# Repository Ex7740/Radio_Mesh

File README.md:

# Radio Mesh

A custom mesh network utilising 2.4GHz radio nodes using microcontrollers and nrf24l01

There are 3 types of node:

# Basic node: 
Simply just the microcontroller and nrf24l01 modules 

# Sensor node: 
More complex, Houses the microcontroller and nrf24l01, plus a varity of sensors, dependant on the application

# Storage node: 
Houses a Flash chip to hold sensor data and other data

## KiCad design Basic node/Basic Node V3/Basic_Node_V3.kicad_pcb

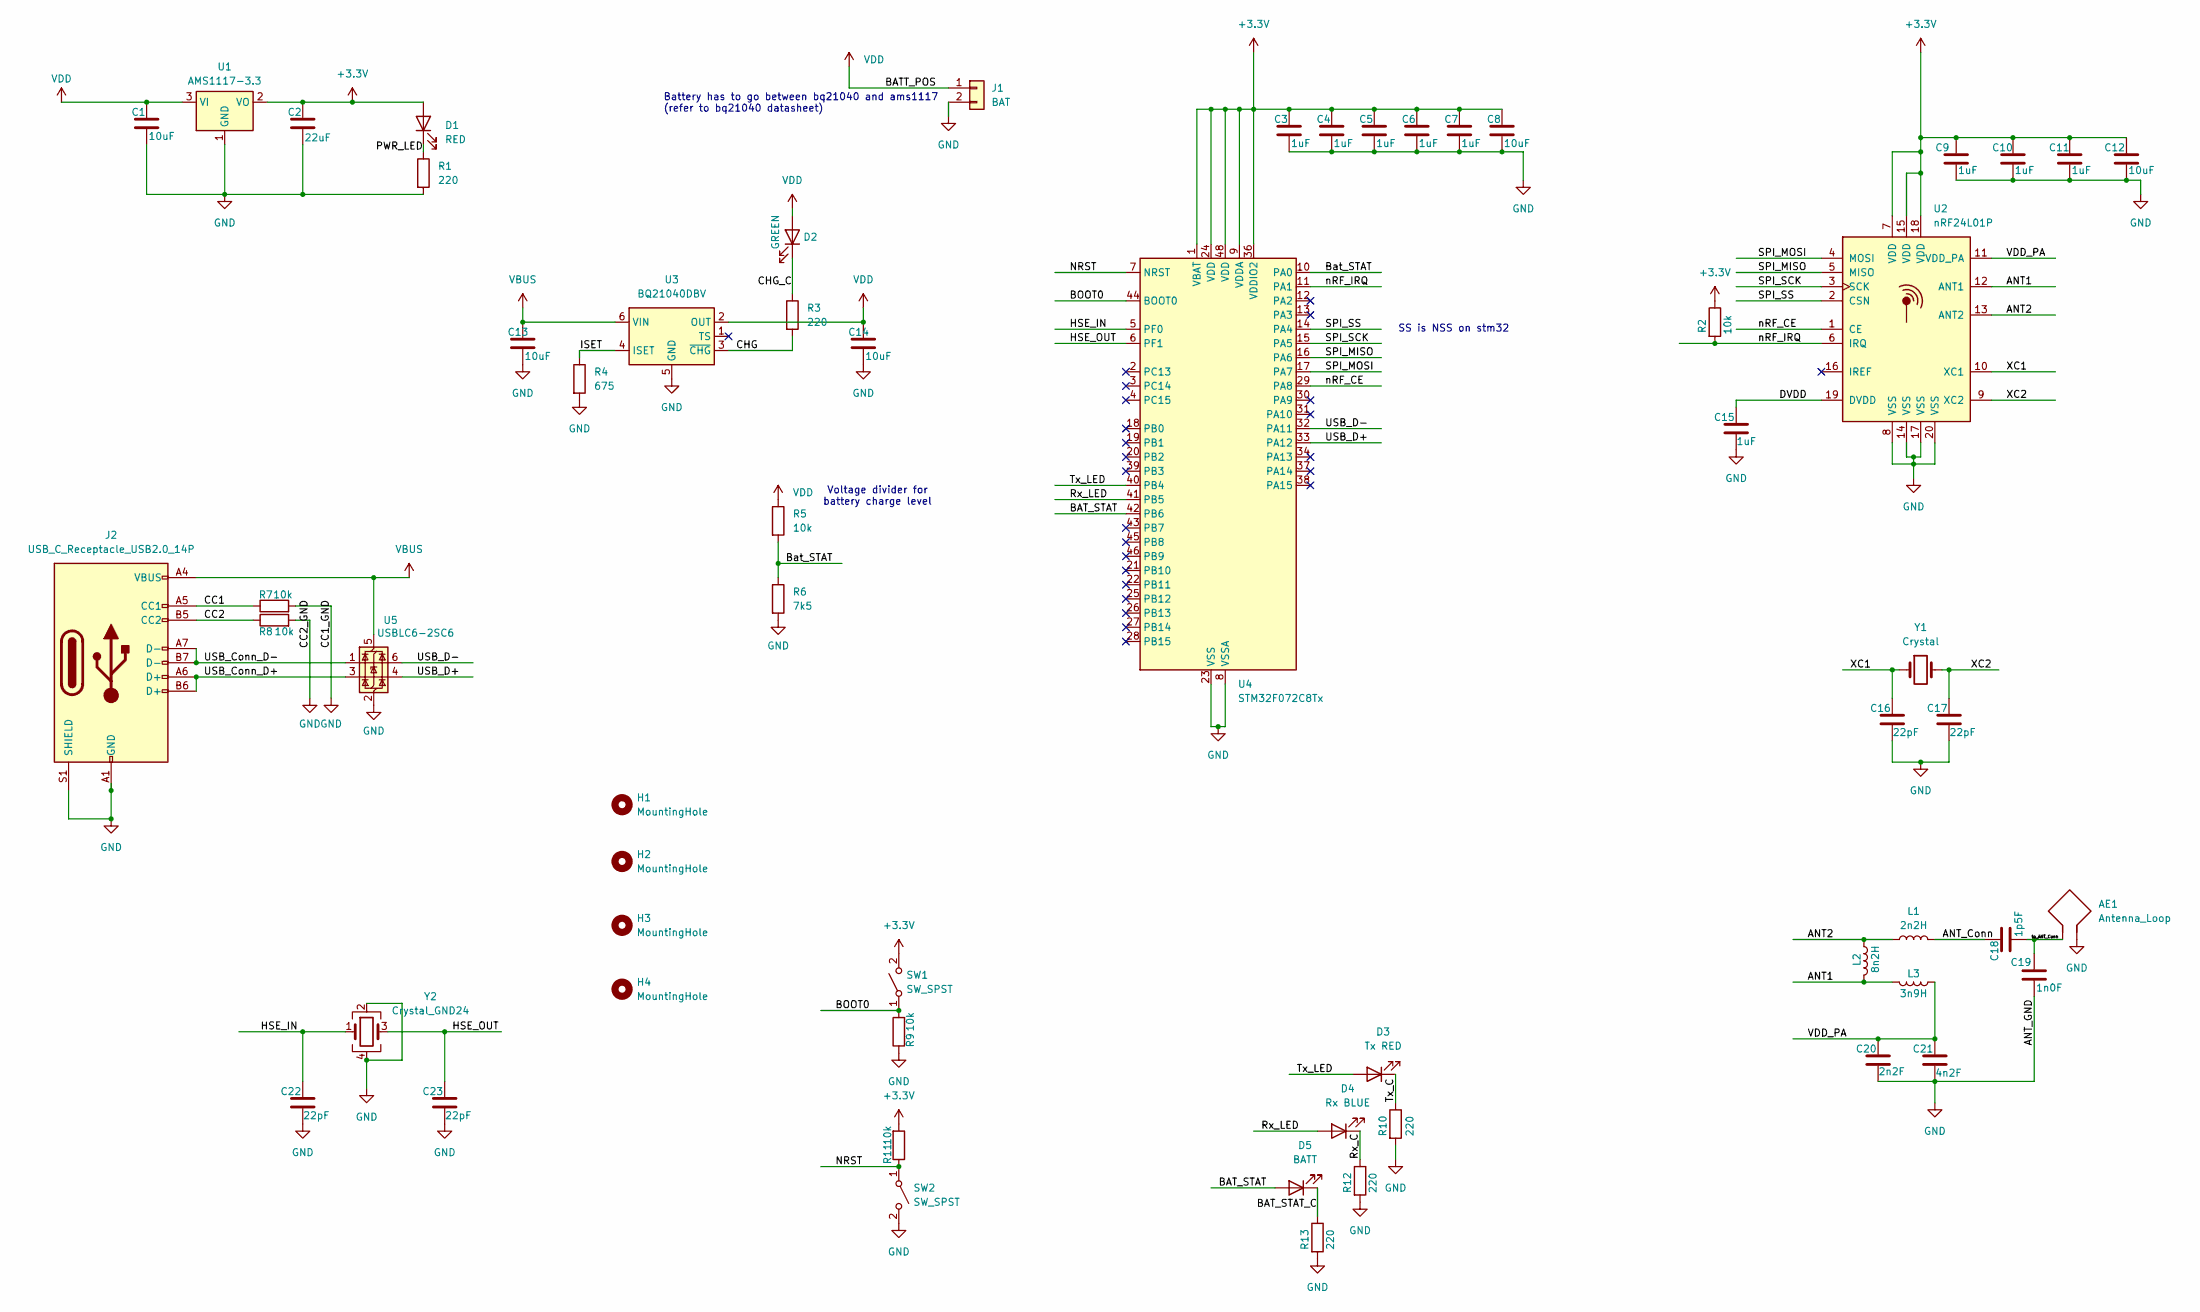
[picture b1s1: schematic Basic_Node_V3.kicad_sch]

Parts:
AE1: Antenna_Loop; Texas_SWRA117D_2.4GHz_Left
C1, C14: 10uF; C_0402_1005Metric
C2: 22uF; C_0402_1005Metric
C3, C4, C5, C6, C7, C9, C10, C11, C15: 1uF; C_0402_1005Metric
C8, C12, C13: 10uF; C_0603_1608Metric
C16, C17, C22, C23: 22pF; C_0402_1005Metric
C18: 1p5F; C_0402_1005Metric
C19: 1n0F; C_0402_1005Metric
C20: 2n2F; C_0402_1005Metric
C21: 4n2F; C_0402_1005Metric
D1: RED; LED_0603_1608Metric
D2: GREEN; LED_0603_1608Metric
D3: Tx RED; LED_0805_2012Metric
D4: Rx BLUE; LED_0805_2012Metric
D5: BATT; LED_0805_2012Metric
H1, H2, H3, H4: MountingHole; MountingHole_2.2mm_M2
J1: BAT; JST_PH_S2B-PH-K_1x02_P2.00mm_Horizontal
J2: USB_C_Receptacle_USB2.0_14P; USB_C_Receptacle_HRO_TYPE-C-31-M-12
L1: 2n2H; L_0603_1608Metric
L2: 8n2H; L_0603_1608Metric
L3: 3n9H; L_0603_1608Metric
R1, R3, R10, R12, R13: 220; R_0603_1608Metric
R2, R5, R8, R9, R11: 10k; R_0603_1608Metric
R4: 675; R_0603_1608Metric
R6: 7k5; R_0603_1608Metric
R7: 10k; L_0603_1608Metric
SW1, SW2: SW_SPST; SW_PUSH_6mm
U1: AMS1117-3.3; SOT-223-3_TabPin2
U2: nRF24L01P; QFN-20-1EP_4x4mm_P0.5mm_EP2.5x2.5mm
U3: BQ21040DBV; SOT-23-6
U4: STM32F072C8Tx; LQFP-48_7x7mm_P0.5mm
U5: USBLC6-2SC6; SOT-23-6
Y1: Crystal; Crystal_SMD_0603-2Pin_6.0x3.5mm
Y2: Crystal_GND24; Crystal_SMD_0603-4Pin_6.0x3.5mm

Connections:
+3.3V: C2.1, C3.1, C4.1, C5.1, C6.1, C7.1, C8.1, C9.1, C10.1, C11.1, C12.1, D1.2 (A), R2.1, R11.2, SW1.2 (B), U1.2 (VO), U2.7 (VDD), U2.15 (VDD), U2.18 (VDD), U4.1 (VBAT), U4.9 (VDDA), U4.24 (VDD), U4.36 (VDDIO2), U4.48 (VDD)
/ANT1: L2.2, L3.2, U2.12 (ANT1)
/ANT2: L1.1, L2.1, U2.13 (ANT2)
/ANT_Conn: C18.1, L1.2
/BAT_STAT: D5.2 (A), U4.42 (PB6)
/BAT_STAT_C: D5.1 (K), R13.1
/BOOT0: R9.2, SW1.1 (A), U4.44 (BOOT0)
/Bat_STAT: R5.2, R6.1, U4.10 (PA0)
/CC1: J2.A5 (CC1), R7.1
/CC2: J2.B5 (CC2), R8.1
/CHG: R3.2, U3.3 (~CHG)
/CHG_C: D2.1 (K), R3.1
/DVDD: C15.1, U2.19 (DVDD)
/HSE_IN: C22.1, U4.5 (PF0), Y2.1
/HSE_OUT: C23.1, U4.6 (PF1), Y2.3
/ISET: R4.1, U3.4 (ISET)
/NRST: R11.1, SW2.1 (A), U4.7 (NRST)
/PWR_LED: D1.1 (K), R1.1
/Rx_C: D4.1 (K), R12.1
/Rx_LED: D4.2 (A), U4.41 (PB5)
/SPI_MISO: U2.5 (MISO), U4.16 (PA6)
/SPI_MOSI: U2.4 (MOSI), U4.17 (PA7)
/SPI_SCK: U2.3 (SCK), U4.15 (PA5)
/SPI_SS: U2.2 (CSN), U4.14 (PA4)
/Tx_C: D3.1 (K), R10.1
/Tx_LED: D3.2 (A), U4.40 (PB4)
/USB_Conn_D+: J2.A6 (D+), J2.B6 (D+), U5.3 (I/O2)
/USB_Conn_D-: J2.A7 (D-), J2.B7 (D-), U5.1 (I/O1)
/USB_D+: U4.33 (PA12), U5.4 (I/O2)
/USB_D-: U4.32 (PA11), U5.6 (I/O1)
/VDD_PA: C20.1, C21.1, L3.1, U2.11 (VDD_PA)
/XC1: C16.1, U2.10 (XC1), Y1.1
/XC2: C17.1, U2.9 (XC2), Y1.2
/nRF_CE: U2.1 (CE), U4.29 (PA8)
/nRF_IRQ: R2.2, U2.6 (IRQ), U4.11 (PA1)
/to_ANT_Conn: AE1.1, C18.2, C19.1
GND: AE1.2, C1.2, C2.2, C3.2, C4.2, C5.2, C6.2, C7.2, C8.2, C9.2, C10.2, C11.2, C12.2, C13.2, C14.2, C15.2, C16.2, C17.2, C19.2, C20.2, C21.2, C22.2, C23.2, J1.2, J2.A1 (GND), J2.A12 (GND), J2.B1 (GND), J2.B12 (GND), J2.S1 (SHIELD), R1.2, R4.2, R6.2, R7.2, R8.2, R9.1, R10.2, R12.2, R13.2, SW2.2 (B), U1.1 (GND), U2.8 (VSS), U2.14 (VSS), U2.17 (VSS), U2.20 (VSS), U3.5 (GND), U4.8 (VSSA), U4.23 (VSS), U4.35 (VSS), U4.47 (VSS), U5.2 (GND), Y2.2, Y2.4
VBUS: C13.1, J2.A4 (VBUS), J2.A9 (VBUS), J2.B4 (VBUS), J2.B9 (VBUS), U3.6 (VIN), U5.5 (VBUS)
VDD: C1.1, C14.1, D2.2 (A), J1.1, R5.1, U1.3 (VI), U3.2 (OUT)

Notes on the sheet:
Voltage divider for battery charge level
Battery has to go between bq21040 and ams1117 (refer to bq21040 datasheet)
SS is NSS on stm32

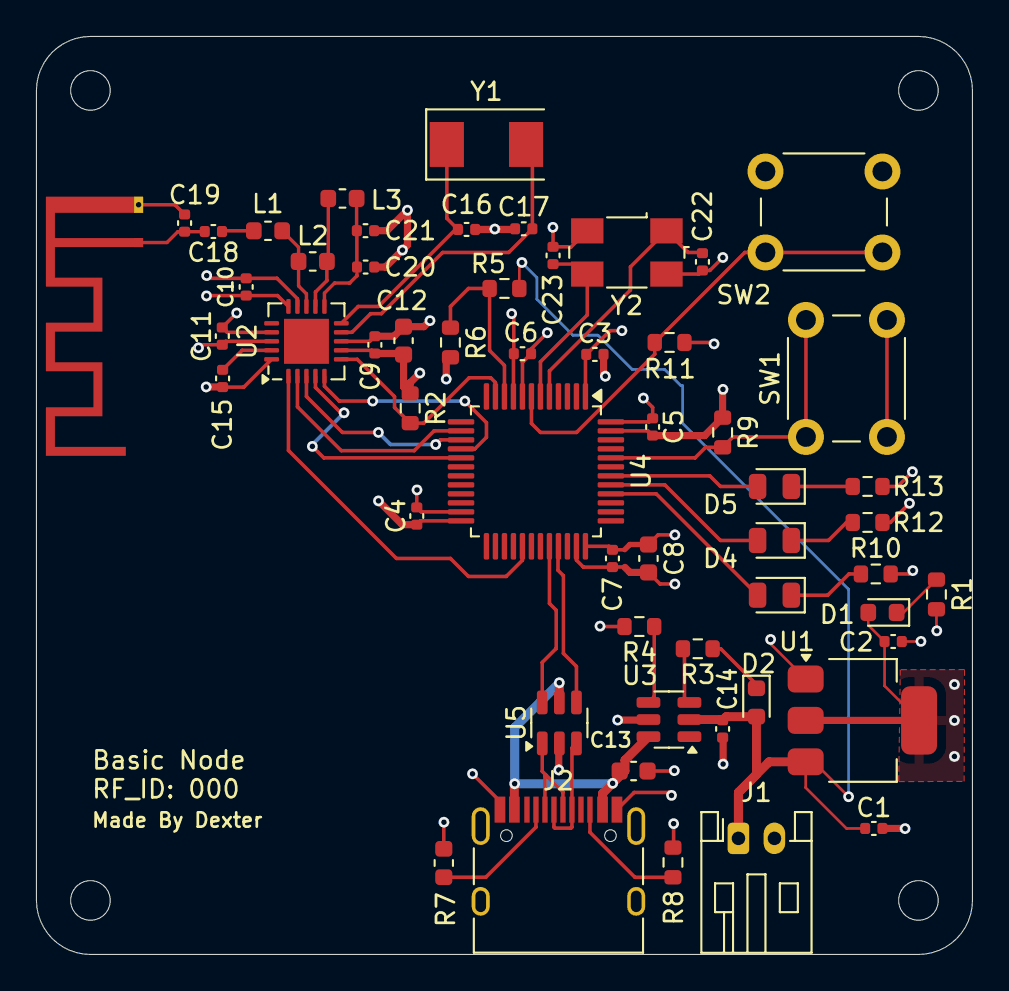
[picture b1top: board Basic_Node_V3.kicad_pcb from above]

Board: 4 copper layers, 52.0 x 51.0 mm, 60 parts (0 on the bottom side), 39 nets.

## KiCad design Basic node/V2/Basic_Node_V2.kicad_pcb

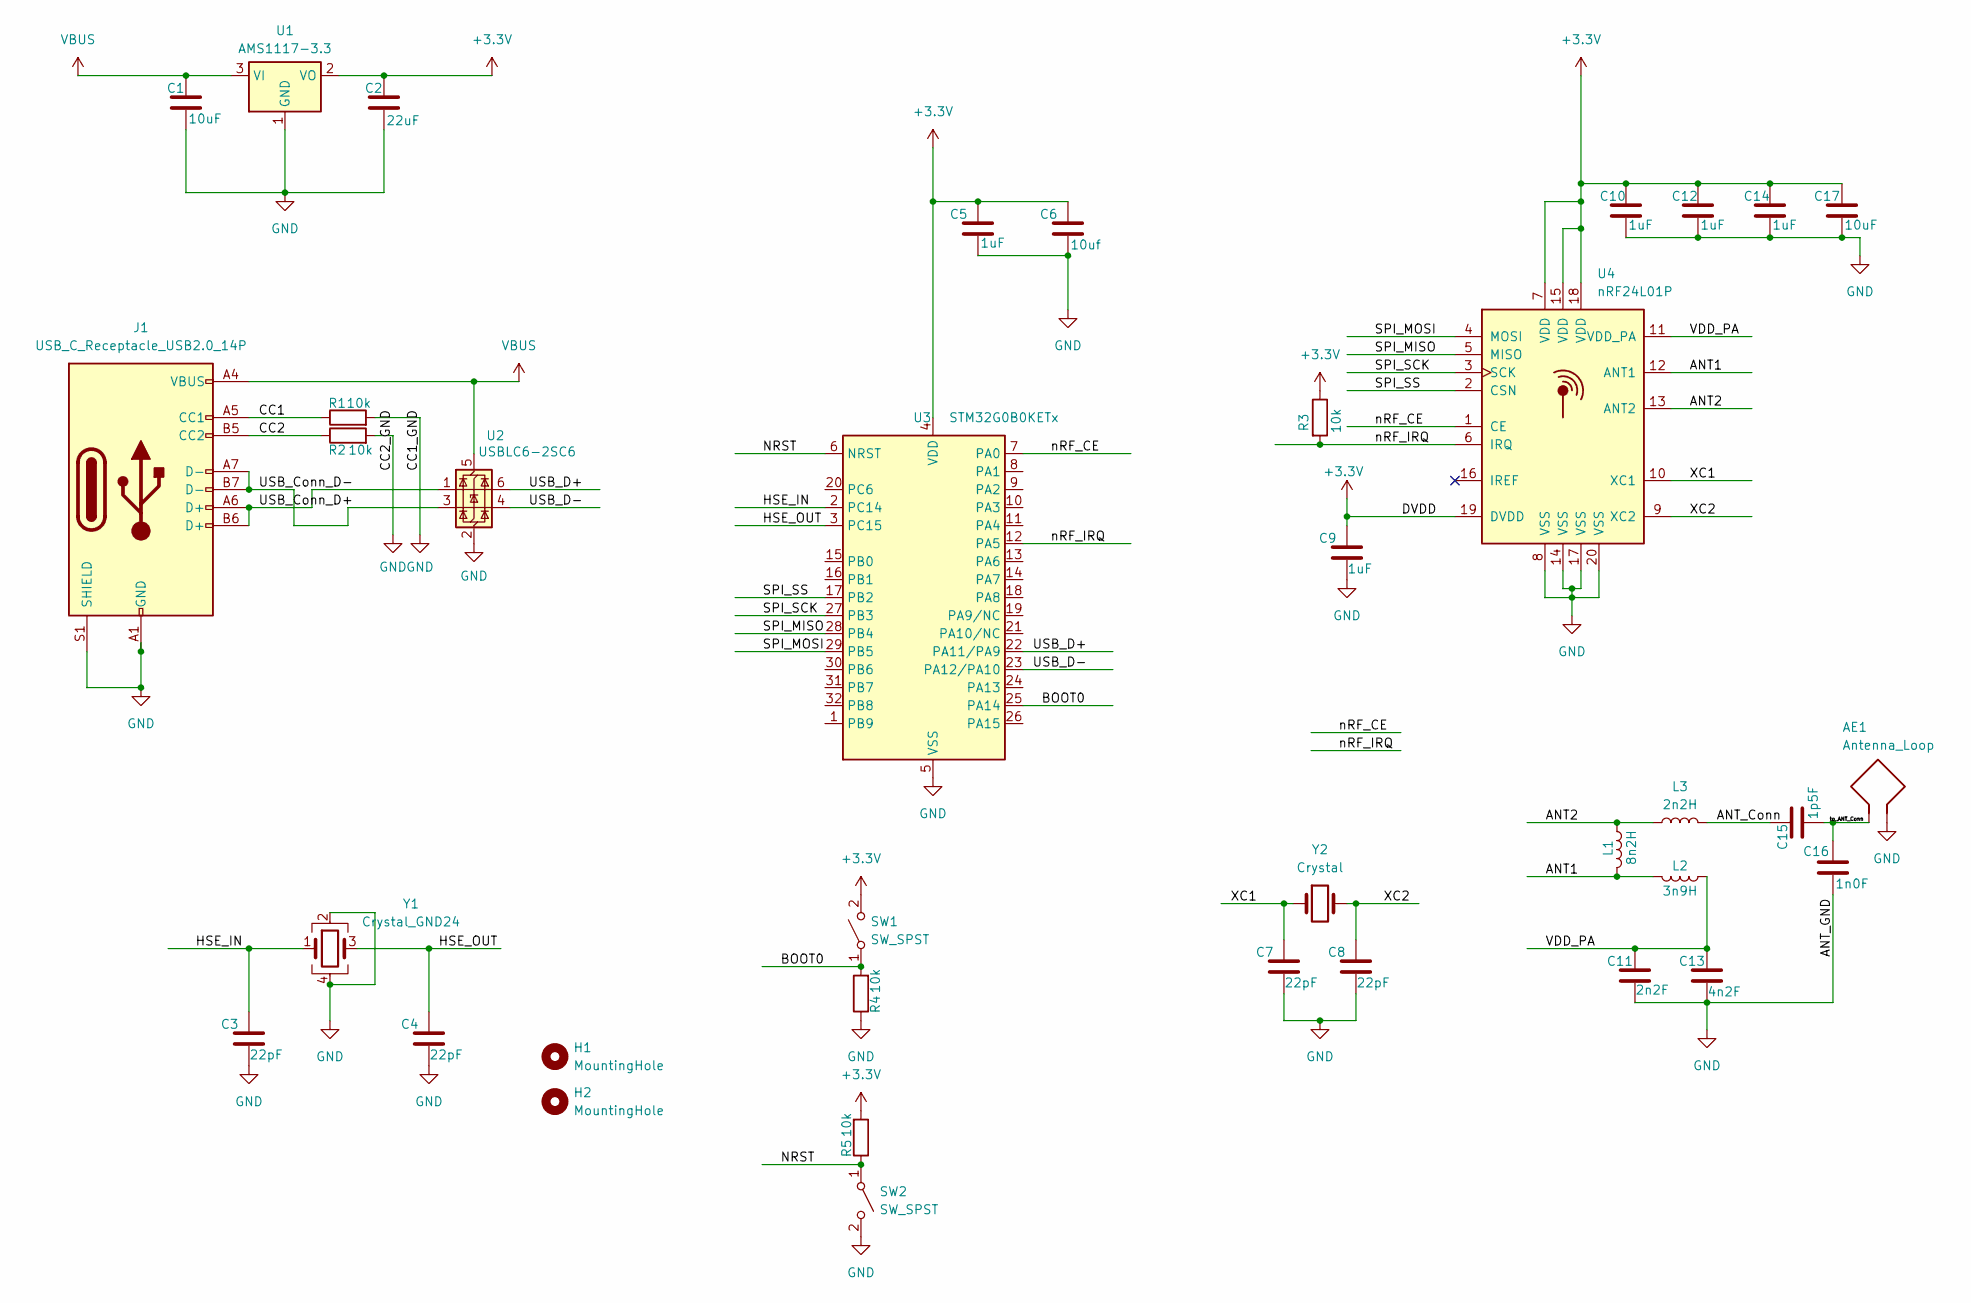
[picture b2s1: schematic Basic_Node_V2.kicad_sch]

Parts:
AE1: Antenna_Loop; Texas_SWRA117D_2.4GHz_Left
C1: 10uF; C_0402_1005Metric
C2: 22uF; C_0402_1005Metric
C3, C4, C7, C8: 22pF; C_0402_1005Metric
C5, C9, C10, C12, C14: 1uF; C_0402_1005Metric
C6: 10uf; C_0603_1608Metric
C11: 2n2F; C_0402_1005Metric
C13: 4n2F; C_0402_1005Metric
C15: 1p5F; C_0402_1005Metric
C16: 1n0F; C_0402_1005Metric
C17: 10uF; C_0603_1608Metric
H1, H2: MountingHole; MountingHole_2.2mm_M2
J1: USB_C_Receptacle_USB2.0_14P; USB_C_Receptacle_HRO_TYPE-C-31-M-12
L1: 8n2H; L_0603_1608Metric
L2: 3n9H; L_0603_1608Metric
L3: 2n2H; L_0603_1608Metric
R1: 10k; L_0603_1608Metric
R2, R3, R4, R5: 10k; R_0603_1608Metric
SW1, SW2: SW_SPST; SW_PUSH_6mm
U1: AMS1117-3.3; SOT-223-3_TabPin2
U2: USBLC6-2SC6; SOT-23-6
U3: STM32G0B0KETx; LQFP-32_7x7mm_P0.8mm
U4: nRF24L01P; QFN-20-1EP_4x4mm_P0.5mm_EP2.5x2.5mm
Y1: Crystal_GND24; Crystal_SMD_0603-4Pin_6.0x3.5mm
Y2: Crystal; Crystal_SMD_0603-2Pin_6.0x3.5mm

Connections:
+3.3V: C2.1, C5.1, C6.1, C9.1, C10.1, C12.1, C14.1, C17.1, R3.1, R5.2, SW1.2 (B), U1.2 (VO), U3.4 (VDD), U4.7 (VDD), U4.15 (VDD), U4.18 (VDD), U4.19 (DVDD)
/ANT1: L1.2, L2.2, U4.12 (ANT1)
/ANT2: L1.1, L3.1, U4.13 (ANT2)
/ANT_Conn: C15.1, L3.2
/BOOT0: R4.2, SW1.1 (A), U3.25 (PA14)
/CC1: J1.A5 (CC1), R1.1
/CC2: J1.B5 (CC2), R2.1
/HSE_IN: C3.1, U3.2 (PC14), Y1.1
/HSE_OUT: C4.1, U3.3 (PC15), Y1.3
/NRST: R5.1, SW2.1 (A), U3.6 (NRST)
/SPI_MISO: U3.28 (PB4), U4.5 (MISO)
/SPI_MOSI: U3.29 (PB5), U4.4 (MOSI)
/SPI_SCK: U3.27 (PB3), U4.3 (SCK)
/SPI_SS: U3.17 (PB2), U4.2 (CSN)
/USB_Conn_D+: J1.A6 (D+), J1.B6 (D+), U2.1 (I/O1)
/USB_Conn_D-: J1.A7 (D-), J1.B7 (D-), U2.3 (I/O2)
/USB_D+: U2.6 (I/O1), U3.22 (PA11/PA9)
/USB_D-: U2.4 (I/O2), U3.23 (PA12/PA10)
/VDD_PA: C11.1, C13.1, L2.1, U4.11 (VDD_PA)
/XC1: C7.1, U4.10 (XC1), Y2.1
/XC2: C8.1, U4.9 (XC2), Y2.2
/nRF_CE: U3.7 (PA0), U4.1 (CE)
/nRF_IRQ: R3.2, U3.12 (PA5), U4.6 (IRQ)
/to_ANT_Conn: AE1.1, C15.2, C16.1
GND: AE1.2, C1.2, C2.2, C3.2, C4.2, C5.2, C6.2, C7.2, C8.2, C9.2, C10.2, C11.2, C12.2, C13.2, C14.2, C16.2, C17.2, J1.A1 (GND), J1.A12 (GND), J1.B1 (GND), J1.B12 (GND), J1.S1 (SHIELD), R1.2, R2.2, R4.1, SW2.2 (B), U1.1 (GND), U2.2 (GND), U3.5 (VSS), U4.8 (VSS), U4.14 (VSS), U4.17 (VSS), U4.20 (VSS), Y1.2, Y1.4
VBUS: C1.1, J1.A4 (VBUS), J1.A9 (VBUS), J1.B4 (VBUS), J1.B9 (VBUS), U1.3 (VI), U2.5 (VBUS)

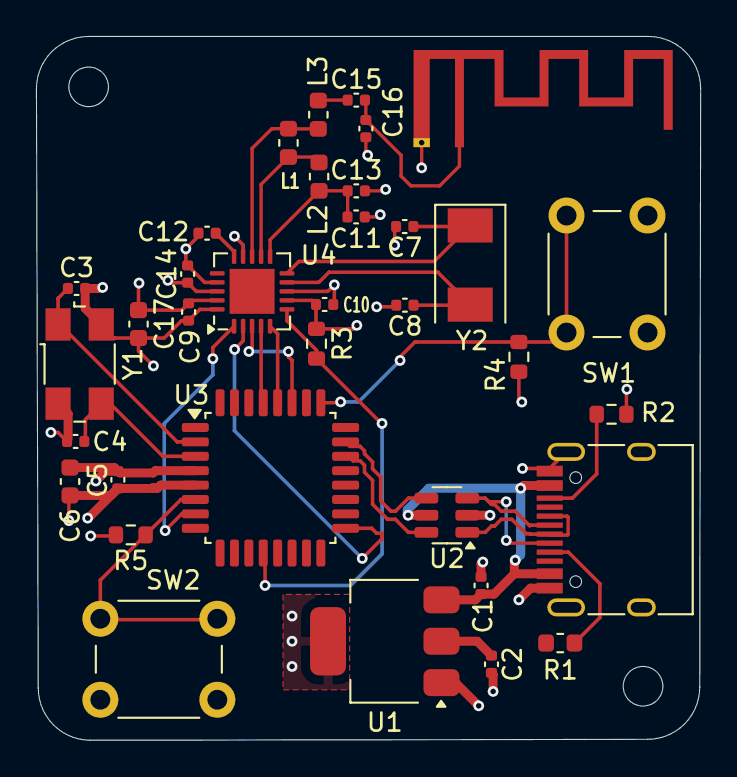
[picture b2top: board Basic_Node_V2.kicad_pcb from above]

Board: 4 copper layers, 36.9 x 39.1 mm, 37 parts (0 on the bottom side), 26 nets.

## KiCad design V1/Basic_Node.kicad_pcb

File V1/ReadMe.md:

# V1 of the node for the radio mesh

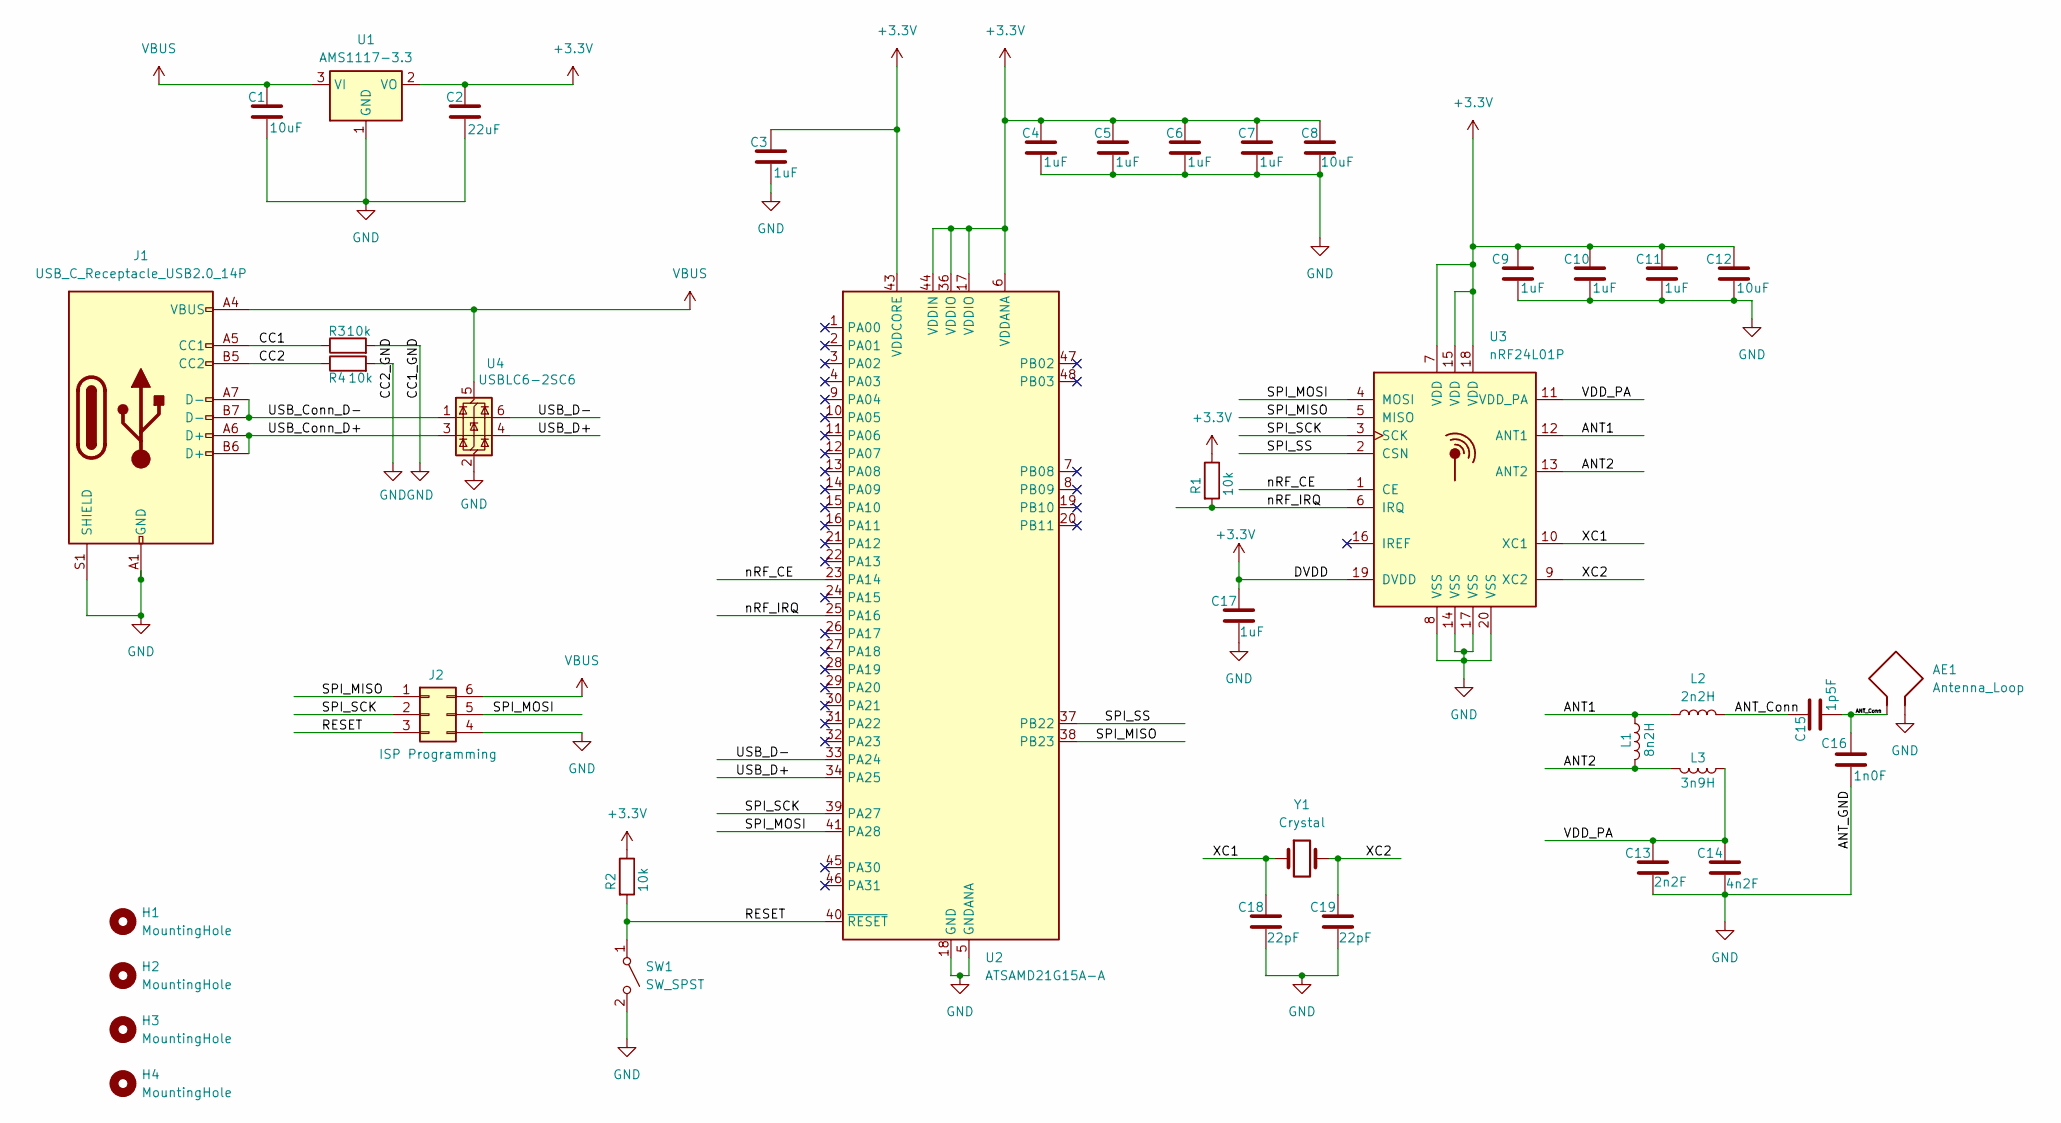
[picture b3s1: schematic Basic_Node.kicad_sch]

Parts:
AE1: Antenna_Loop; Texas_SWRA117D_2.4GHz_Left
C1, C8, C12: 10uF; C_0402_1005Metric
C2: 22uF; C_0402_1005Metric
C3, C4, C5, C6, C7, C9, C10, C11, C17: 1uF; C_0402_1005Metric
C13: 2n2F; C_0402_1005Metric
C14: 4n2F; C_0402_1005Metric
C15: 1p5F; C_0402_1005Metric
C16: 1n0F; C_0402_1005Metric
C18, C19: 22pF; C_0402_1005Metric
H1, H2, H3, H4: MountingHole; MountingHole_2.2mm_M2
J1: USB_C_Receptacle_USB2.0_14P; USB_C_Receptacle_HRO_TYPE-C-31-M-12
J2: ISP Programming; PinHeader_2x03_P2.54mm_Vertical
L1: 8n2H; L_0402_1005Metric
L2: 2n2H; L_0402_1005Metric
L3: 3n9H; L_0402_1005Metric
R1, R2, R3, R4: 10k; R_0402_1005Metric
SW1: SW_SPST; SW_SPST_PTS647_Sx38
U1: AMS1117-3.3; SOT-223-3_TabPin2
U2: ATSAMD21G15A-A; TQFP-48_7x7mm_P0.5mm
U3: nRF24L01P; QFN-20-1EP_4x4mm_P0.5mm_EP2.5x2.5mm
U4: USBLC6-2SC6; SOT-23-6
Y1: Crystal; Crystal_SMD_0603-2Pin_6.0x3.5mm

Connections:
+3.3V: C2.1, C3.1, C4.1, C5.2, C6.1, C7.1, C8.1, C9.1, C10.1, C11.1, C12.1, C17.1, R1.1, R2.1, U1.2 (VO), U2.6 (VDDANA), U2.17 (VDDIO), U2.36 (VDDIO), U2.43 (VDDCORE), U2.44 (VDDIN), U3.7 (VDD), U3.15 (VDD), U3.18 (VDD), U3.19 (DVDD)
/ANT1: L1.1, L2.1, U3.12 (ANT1)
/ANT2: L1.2, L3.2, U3.13 (ANT2)
/ANT_Conn: AE1.1, C15.1, C15.2, C16.1, L2.2
/CC1: J1.A5 (CC1), R3.1
/CC2: J1.B5 (CC2), R4.1
/RESET: J2.3, R2.2, SW1.1 (A), U2.40 (~RESET)
/SPI_MISO: J2.1, U2.38 (PB23), U3.5 (MISO)
/SPI_MOSI: J2.5, U2.41 (PA28), U3.4 (MOSI)
/SPI_SCK: J2.2, U2.39 (PA27), U3.3 (SCK)
/SPI_SS: U2.37 (PB22), U3.2 (CSN)
/USB_Conn_D+: J1.A6 (D+), J1.B6 (D+), U4.3 (I/O2)
/USB_Conn_D-: J1.A7 (D-), J1.B7 (D-), U4.1 (I/O1)
/USB_D+: U2.34 (PA25), U4.4 (I/O2)
/USB_D-: U2.33 (PA24), U4.6 (I/O1)
/VDD_PA: C13.1, C14.1, L3.1, U3.11 (VDD_PA)
/XC1: C18.1, U3.10 (XC1), Y1.1
/XC2: C19.1, U3.9 (XC2), Y1.2
/nRF_CE: U2.23 (PA14), U3.1 (CE)
/nRF_IRQ: R1.2, U2.25 (PA16), U3.6 (IRQ)
GND: AE1.2, C1.2, C2.2, C3.2, C4.2, C5.1, C6.2, C7.2, C8.2, C9.2, C10.2, C11.2, C12.2, C13.2, C14.2, C16.2, C17.2, C18.2, C19.2, J1.A1 (GND), J1.A12 (GND), J1.B1 (GND), J1.B12 (GND), J1.S1 (SHIELD), J2.4, R3.2, R4.2, SW1.2 (B), U1.1 (GND), U2.5 (GNDANA), U2.18 (GND), U2.35 (GND), U2.42 (GND), U3.8 (VSS), U3.14 (VSS), U3.17 (VSS), U3.20 (VSS), U4.2 (GND)
VBUS: C1.1, J1.A4 (VBUS), J1.A9 (VBUS), J1.B4 (VBUS), J1.B9 (VBUS), J2.6, U1.3 (VI), U4.5 (VBUS)

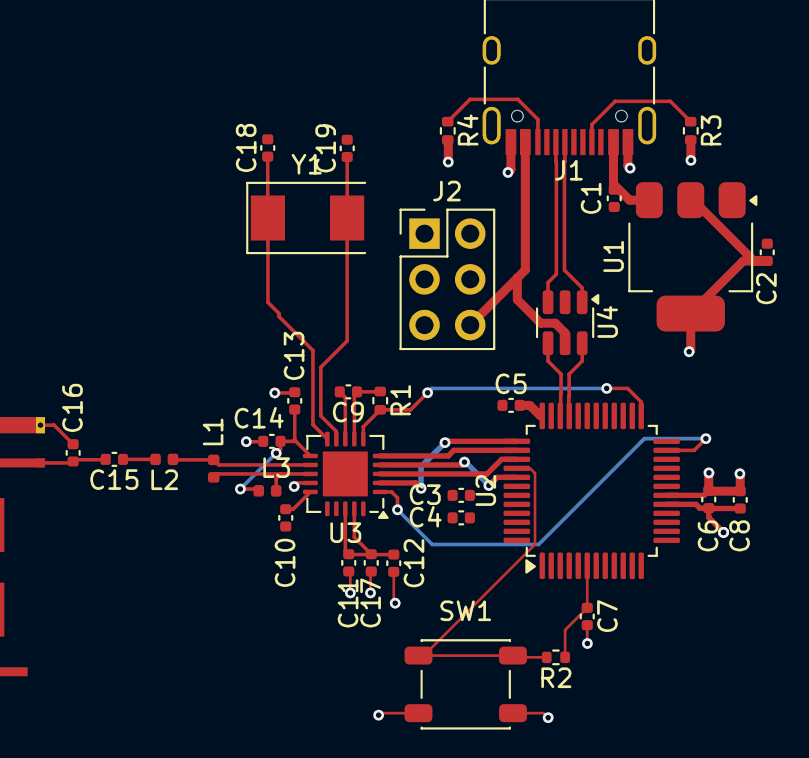
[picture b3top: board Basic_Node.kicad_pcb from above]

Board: 4 copper layers, 39 parts (0 on the bottom side), 22 nets.

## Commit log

2024-10-15 Basic Node V1
